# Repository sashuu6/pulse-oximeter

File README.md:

# Pulse Oximeter

## Introduction

This project is DIY pulse oximeter sensor developed using MAX30100 sensor.

## Folder Structure

1. docs/top.png : PCB Board top Design
2. docs/bottom.png : PCB Board bottom design
3. docs/drills.png : PCB Board drills design
4. eagle-design : PCB design
5. html-template : HTML report template used in ino.
6. pulse-oximeter : Arduino code

## Component Used

1. NodeMCU (x1) - [Tomson Electronics](https://www.tomsonelectronics.com/products/buy-nodemcu-esp8266-esp-12e-with-ch340-online)
2. TP4056 Board (x1) - [FLYROBO](https://www.flyrobo.in/tp4056-1a-li-ion-lithium-battery-charging-module-mini-usb)
3. Resistor (220 Ohms) (x2) - [Tomson Electronics](https://www.tomsonelectronics.com/products/100k-ohm-metal-film-resistor?variant=8737726038107)
4. LED (Red) (x2) - [Tomson Electronics](https://www.tomsonelectronics.com/products/led-basic-red-5mm-pack-of-10)
5. 0.96 Inch OLED Display - [Tomson Electronics](https://www.tomsonelectronics.com/products/0-96-inch-128-x-64-i2c-iic-4pin-oled-display-module-blue)
6. Female headers - [Robu (India)](https://robu.in/product/2mm-pitch-female-berg-strip-40x1-2pcs/)

## PCB Design

### Top Design

### Bottom Design

### Drills Design

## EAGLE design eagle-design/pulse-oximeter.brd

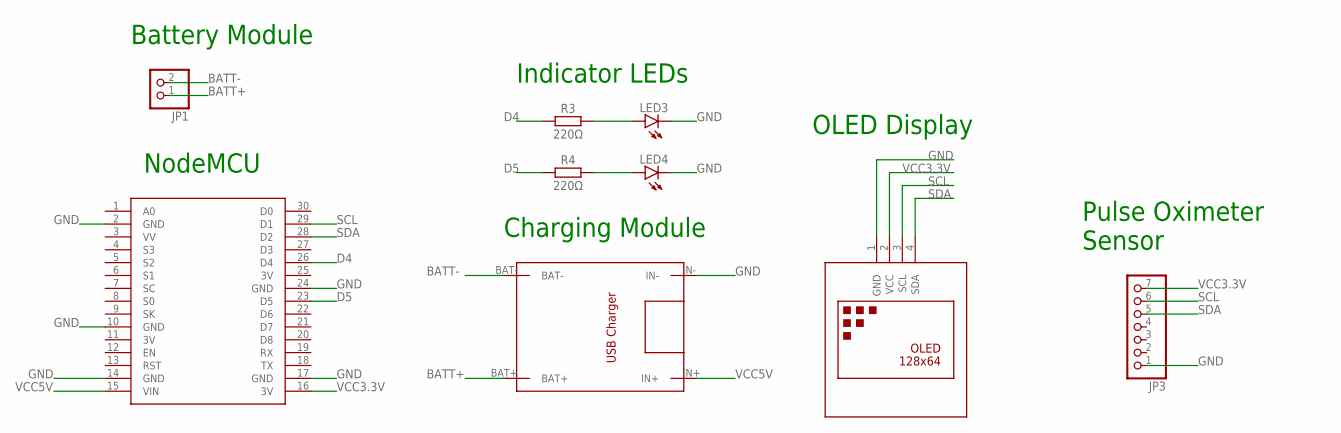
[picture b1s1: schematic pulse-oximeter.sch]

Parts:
JP1: PINHD-1X2; 1X02
JP3: PINHD-1X7; 1X07
LED3, LED4: LED3MM
R3, R4: 220Ω; RESAD1176W63L850D250B
U$1: DISPLAY-OLED-128X64-I2C
U$2: NODEMCU
U$3: TP4056

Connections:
3V: U$2.11 (3V), U$2.25 (3V)
BATT+: JP1.1, U$3.BAT+
BATT-: JP1.2, U$3.BAT-
D4: R3.1, U$2.26 (D4)
D5: R4.1, U$2.23 (D5)
GND: JP3.1, LED3.K (C), LED4.K (C), U$1.1 (GND), U$2.2 (GND), U$2.10 (GND), U$2.14 (GND), U$2.17 (GND), U$2.24 (GND), U$3.IN-
unnamed: LED3.A, R3.2
unnamed: LED4.A, R4.2
SCL: JP3.6, U$1.3 (SCL), U$2.29 (D1)
SDA: JP3.5, U$1.4 (SDA), U$2.28 (D2)
VCC3.3V: JP3.7, U$1.2 (VCC), U$2.16 (3V)
VCC5V: U$2.15 (VIN), U$3.IN+

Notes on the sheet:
NodeMCU
Charging Module
Indicator LEDs
Battery Module
OLED Display
Pulse Oximeter Sensor

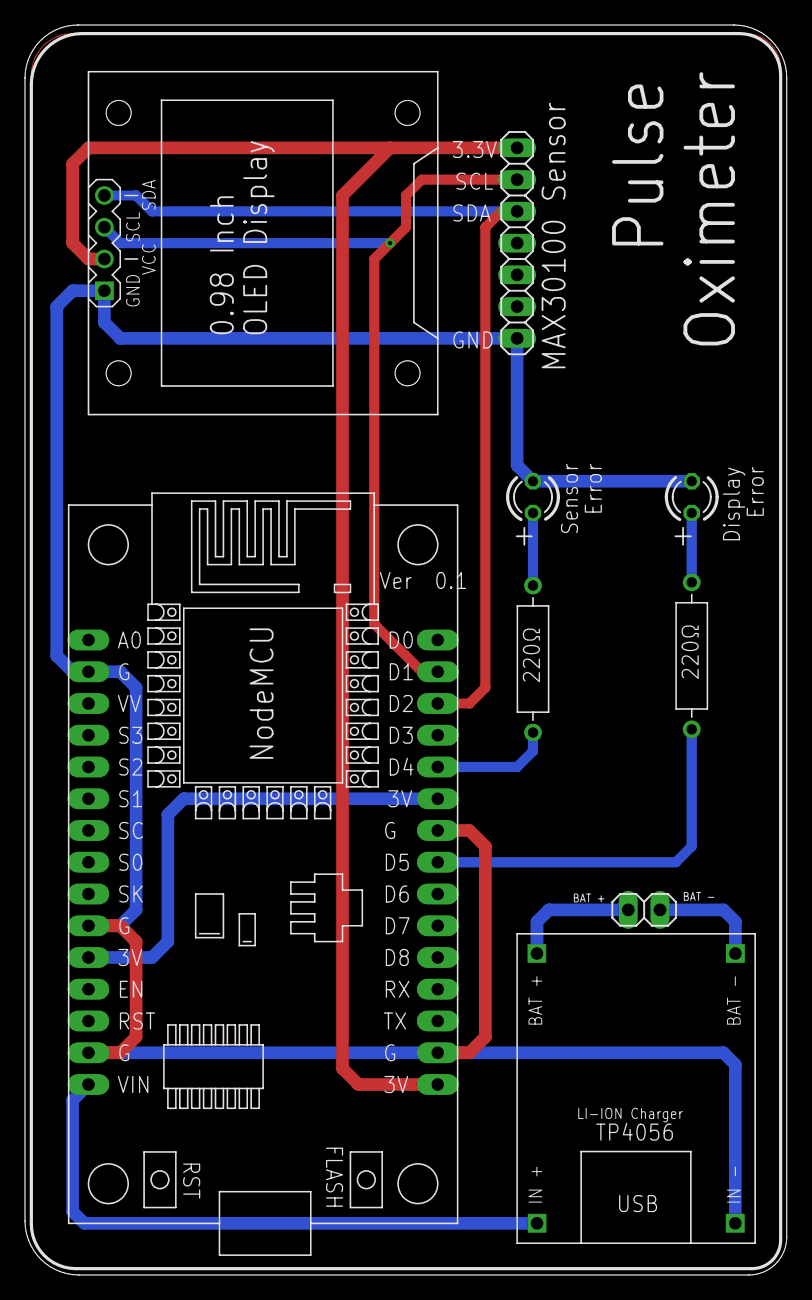
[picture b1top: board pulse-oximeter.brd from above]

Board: 2 copper layers, 60.9 x 100.0 mm, 9 parts (0 on the bottom side), 12 nets.

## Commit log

2021-05-09 Added arduino code
2021-05-09 Added arduino code and html template
2021-05-09 Added .gitignore
2021-05-09 Added html template
2021-05-09 Added eagle design schematics
2021-06-13 Updated design
2021-06-13 Added new design
2021-07-10 Updated board design
2021-07-10 Added PCB designs
2021-07-10 Updated doc
2021-07-10 Fixed track size
2021-07-31 Added GND plain
2021-07-31 Updated exports
2021-08-22 Added 3.3V top layer
2022-05-03 Added PCB photos
2022-05-03 removed .db file

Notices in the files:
parts and their libraries:
diy-modules: Released under the Creative Commons Attribution 4.0 International License: http://creativecommons.org/licenses/by/4.0
